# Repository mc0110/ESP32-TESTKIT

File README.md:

# ESP32-TESTKIT

## Motivation
Breadboards are the best or most uncomplicated way to prototype, to test electronic circuit parts quickly and easily or to change them without a soldering iron and without losing the components.

The range of applications for ESP8266 and ESP32 is endless. It is fantastic how quickly and easily practical applications can be realised with this nice devices, which are also super easy to address via WiFi or BLE. They are also very cheap and, like many commercial products (e.g. sonoff, shelly), very reliable. 

The possibilities for using these chips are exorbitantly increased by the great ESPHOME project and also further opened up for prototyping, because it allows the otherwise additionally necessary programming to be reduced to the configuration of a single YAML file. Among other things, it offers the possibility of accessing an elegant web interface, which makes prototypes fantastically easy to implement and test, even if the final programming is to be completely changed afterwards.

** But unfortunately breadboards and ESP-DEVKITS don't really go well together. **

However, if you have ever tried to test your application on a breadboard with a normal TestKIT, the result is somewhat frustrating. I would call it the breadboard paradox. The grid dimension of 2.56mm fits, but all contacts are covered and therefore unusable. There is no chance to contact the individual pins of the board. The required pins must be connected to the board as cables. So you will quickly be faced with a multitude of cable connections that bring with them a high potential for errors during testing. In addition, during my experiments with the ESP32, I found that longer cables in particular can lead to problems with the voltage-supplying lines when the chip wants to establish the WiFi connection, for example, as higher current peaks can obviously occur here.

## Problem definition

This project was therefore about keeping the advantages of ESP-DEVKITS, but resolving the paradox described above and making the CPU pins on the breadboard all available. This makes it extremely convenient to supply power directly to the breadboard. Most DEVKITS have a USB micro-connector and supply the board with 5V as well as 3V3. This would be a requirement that should not be waived. The board should also ensure stable operation of the ESP32 chip, ensuring WiFi setup, etc. without brownout detection or crashes. In addition to the supply via a USB adapter, it could also be helpful to be able to use a 3V3 voltage source (Li-Ion, alkaline batteries) directly.

It has also been shown that there is a need for digital inputs and outputs in almost all circuits. For testing circuits, these should be equipped with signal LEDs to make debugging possible without additional measuring devices, auxiliary circuits, test LEDs. But the ESP32 also offers the possibility to use ADCs and DAC. In order to be able to measure voltages above 3.3V, a suitable voltage divider is needed. Here it would be good to have measurable voltages of up to 15V to cover most applications. Achieving an accuracy of 0.01V is no problem with the ESP32. The ADC functions are masterfully supported by [ESPHOME ADC](https://esphome.io/components/sensor/adc.html?highlight=adc) including the AutoRange function. 

## Provided solution

My ESP32-DEVKIT, which I would like to present here, therefore has the following features:

- USB B micro PowerInput or alternatively
- 12V PlugIn PowerInput
- Input power available as own connector for tests
- DC-DC converter to 3V3
- PGM-socket (shelly-compatible)
- RESET button and GPIO00 button
- 4x 15V ADC-ports (with voltage dividers)
  (V1:GPIO39, V2:GPIO36, V3: GPIO35, V4: GPIO34)
- 4x digital output (LED-controlled) vs. GND-level
  (O1:GPIO21, O2: GPIO22, O3: GPIO23, O4: GPIO25)
- 4x digital input (LED-controlled) vs. GND-level
  (I1:GPIO12, I2: GPIO13, I3: GPIO14, I4: GPIO15)

- all ESP-PINs available on the breadboard

Circuit diagram and board are realised in KICAD V6. The board is 2-layered.

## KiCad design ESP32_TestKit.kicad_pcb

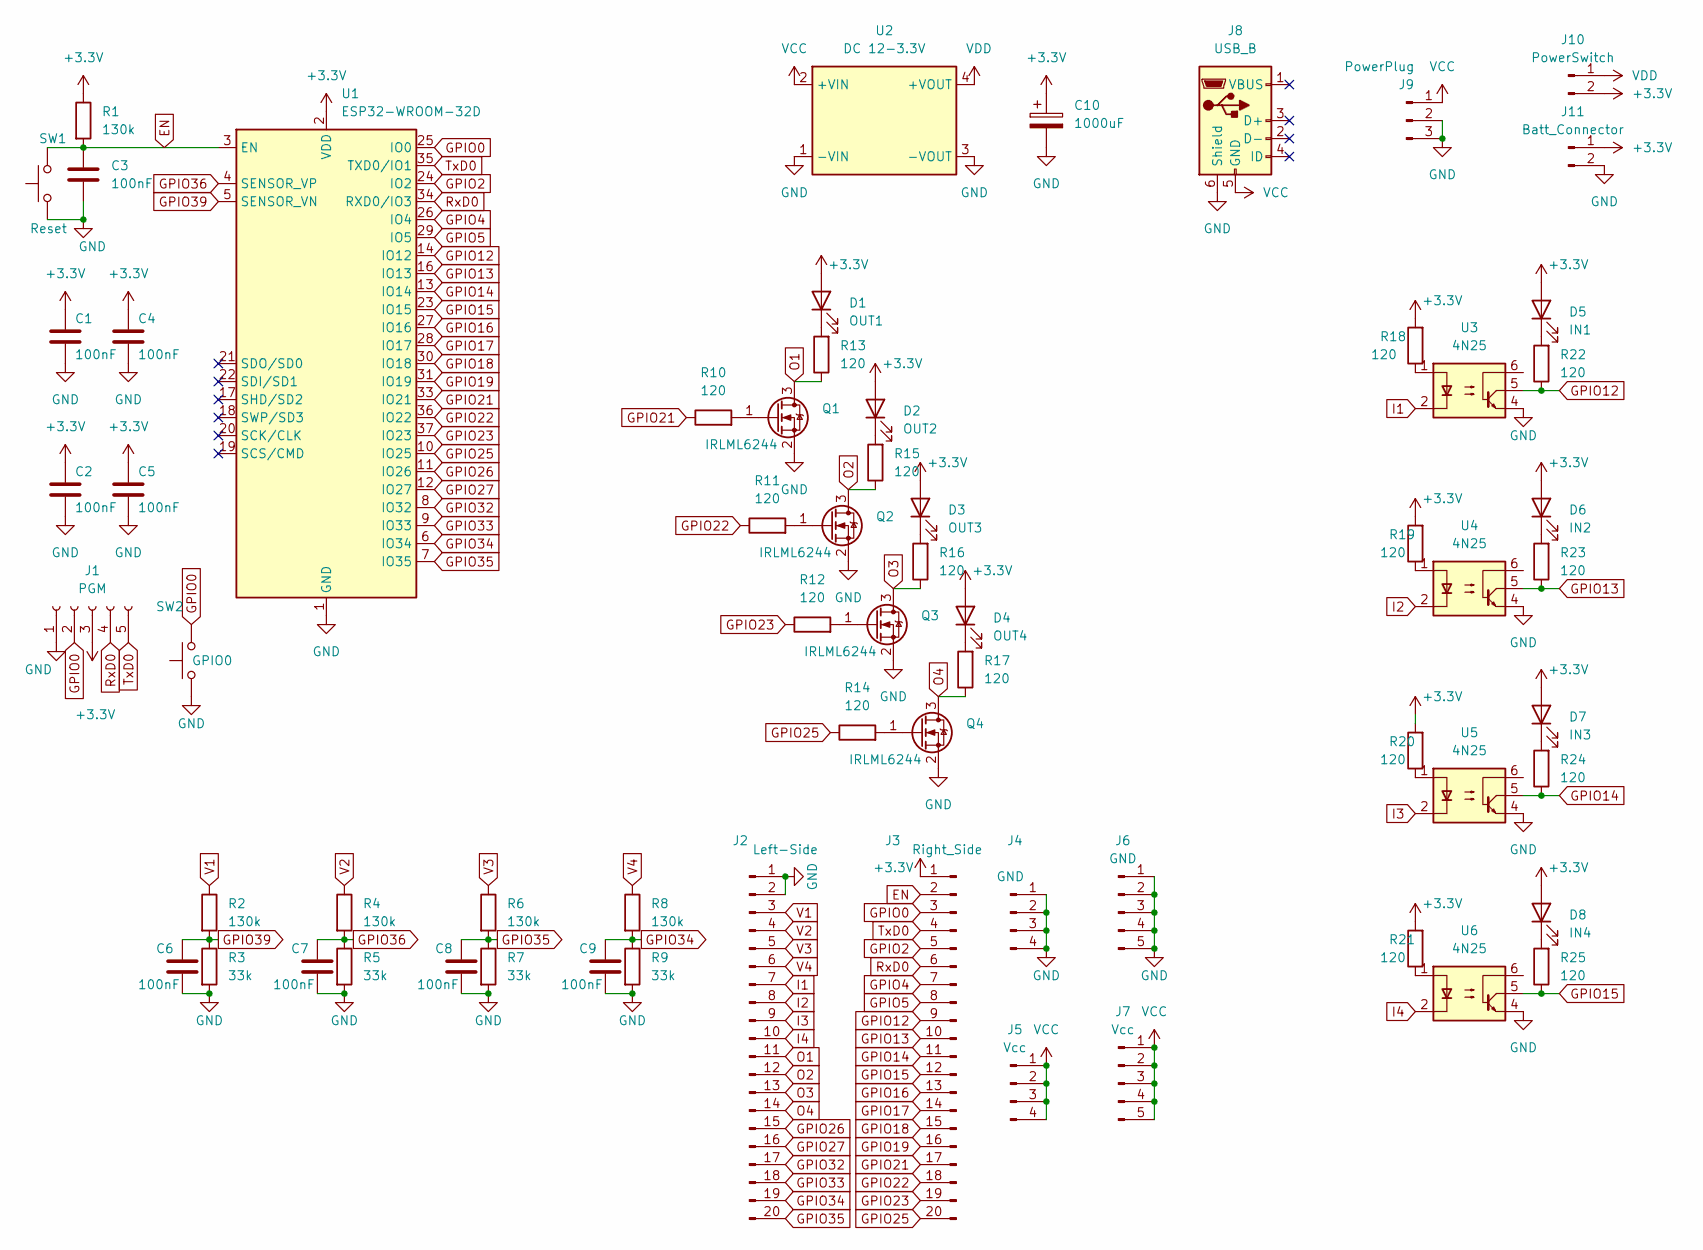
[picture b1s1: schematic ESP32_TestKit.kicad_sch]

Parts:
C1, C2, C3, C4, C5, C6, C7, C8, C9: 100nF; C_Axial_L5.1mm_D3.1mm_P7.50mm_Horizontal
C10: 1000uF; CP_Radial_D10.0mm_P5.00mm
D1: OUT1; LED_D3.0mm
D2: OUT2; LED_D3.0mm
D3: OUT3; LED_D3.0mm
D4: OUT4; LED_D3.0mm
D5: IN1; LED_D3.0mm
D6: IN2; LED_D3.0mm
D7: IN3; LED_D3.0mm
D8: IN4; LED_D3.0mm
J1: PGM; PinSocket_1x05_P2.54mm_Vertical
J2: Left-Side; PinHeader_1x20_P2.54mm_Vertical
J3: Right_Side; PinHeader_1x20_P2.54mm_Vertical
J4: GND; PinHeader_1x04_P2.54mm_Vertical
J5: Vcc; PinHeader_1x04_P2.54mm_Vertical
J6: GND; PinHeader_1x05_P2.54mm_Vertical
J7: Vcc; PinHeader_1x05_P2.54mm_Vertical
J8: USB_B; USB_Micro-AB_Molex_47590-0001
J9: PowerPlug; BarrelJack_GCT_DCJ200-10-A_Horizontal
J10: PowerSwitch; PinHeader_1x02_P2.54mm_Vertical
J11: Batt_Connector; PinHeader_1x02_P2.54mm_Vertical
Q1, Q2, Q3, Q4: IRLML6244; SOT-23
R1, R2, R4, R6, R8: 130k; R_0603_1608Metric
R3, R5, R7, R9: 33k; R_0603_1608Metric
R10, R11, R12, R13, R14, R15, R16, R17, R18, R19, R20, R21, R22, R23, R24, R25: 120; R_0603_1608Metric
SW1: Reset; SW_SPST_PTS645
SW2: GPIO0; SW_SPST_PTS645
U1: ESP32-WROOM-32D; ESP32-WROOM-32
U2: DC 12-3.3V; Converter_DCDC_China3A_THT
U3, U4, U5, U6: 4N25; DIP-6_W7.62mm

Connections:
+3V3: C1.1, C2.1, C4.1, C5.1, C10.1, D1.2 (A), D2.2 (A), D3.2 (A), D4.2 (A), D5.2 (A), D6.2 (A), D7.2 (A), D8.2 (A), J1.3, J3.1, J10.2, J11.1, R1.1, R18.2, R19.2, R20.2, R21.2, U1.2 (VDD)
EN: C3.1, J3.2, R1.2, SW1.2, U1.3 (EN)
GND: C1.2, C2.2, C3.2, C4.2, C5.2, C6.2, C7.2, C8.2, C9.2, C10.2, J1.1, J2.1, J2.2, J4.1, J4.2, J4.3, J4.4, J6.1, J6.2, J6.3, J6.4, J6.5, J8.6 (Shield), J9.2, J9.3, J11.2, Q1.2 (S), Q2.2 (S), Q3.2 (S), Q4.2 (S), R3.2, R5.2, R7.2, R9.2, SW1.1, SW2.1, U1.1 (GND), U1.15 (GND), U1.38 (GND), U1.39 (GND), U2.1 (-VIN), U2.3 (-VOUT), U3.4, U4.4, U5.4, U6.4
GPIO0: J1.2, J3.3, SW2.2, U1.25 (IO0)
GPIO2: J3.5, U1.24 (IO2)
GPIO4: J3.7, U1.26 (IO4)
GPIO5: J3.8, U1.29 (IO5)
GPIO12: J3.9, R22.1, U1.14 (IO12), U3.5
GPIO13: J3.10, R23.1, U1.16 (IO13), U4.5
GPIO14: J3.11, R24.1, U1.13 (IO14), U5.5
GPIO15: J3.12, R25.1, U1.23 (IO15), U6.5
GPIO16: J3.13, U1.27 (IO16)
GPIO17: J3.14, U1.28 (IO17)
GPIO18: J3.15, U1.30 (IO18)
GPIO19: J3.16, U1.31 (IO19)
GPIO21: J3.17, R10.1, U1.33 (IO21)
GPIO22: J3.18, R11.1, U1.36 (IO22)
GPIO23: J3.19, R12.1, U1.37 (IO23)
GPIO25: J3.20, R14.1, U1.10 (IO25)
GPIO26: J2.15, U1.11 (IO26)
GPIO27: J2.16, U1.12 (IO27)
GPIO32: J2.17, U1.8 (IO32)
GPIO33: J2.18, U1.9 (IO33)
GPIO34: C9.1, J2.19, R8.2, R9.1, U1.6 (IO34)
GPIO35: C8.1, J2.20, R6.2, R7.1, U1.7 (IO35)
GPIO36: C7.1, R4.2, R5.1, U1.4 (SENSOR_VP)
GPIO39: C6.1, R2.2, R3.1, U1.5 (SENSOR_VN)
I1: J2.7, U3.2
I2: J2.8, U4.2
I3: J2.9, U5.2
I4: J2.10, U6.2
unnamed: D1.1 (K), R13.2
unnamed: D2.1 (K), R15.2
unnamed: D3.1 (K), R16.2
unnamed: D4.1 (K), R17.2
unnamed: D5.1 (K), R22.2
unnamed: D6.1 (K), R23.2
unnamed: D7.1 (K), R24.2
unnamed: D8.1 (K), R25.2
unnamed: Q1.1 (G), R10.2
unnamed: Q2.1 (G), R11.2
unnamed: Q3.1 (G), R12.2
unnamed: Q4.1 (G), R14.2
unnamed: R18.1, U3.1
unnamed: R19.1, U4.1
unnamed: R20.1, U5.1
unnamed: R21.1, U6.1
O1: J2.11, Q1.3 (D), R13.1
O2: J2.12, Q2.3 (D), R15.1
O3: J2.13, Q3.3 (D), R16.1
O4: J2.14, Q4.3 (D), R17.1
RxD0: J1.4, J3.6, U1.34 (RXD0/IO3)
TxD0: J1.5, J3.4, U1.35 (TXD0/IO1)
V1: J2.3, R2.1
V2: J2.4, R4.1
V3: J2.5, R6.1
V4: J2.6, R8.1
VCC: J5.1, J5.2, J5.3, J5.4, J7.1, J7.2, J7.3, J7.4, J7.5, J8.5 (GND), J9.1, U2.2 (+VIN)
VDD: J10.1, U2.4 (+VOUT)

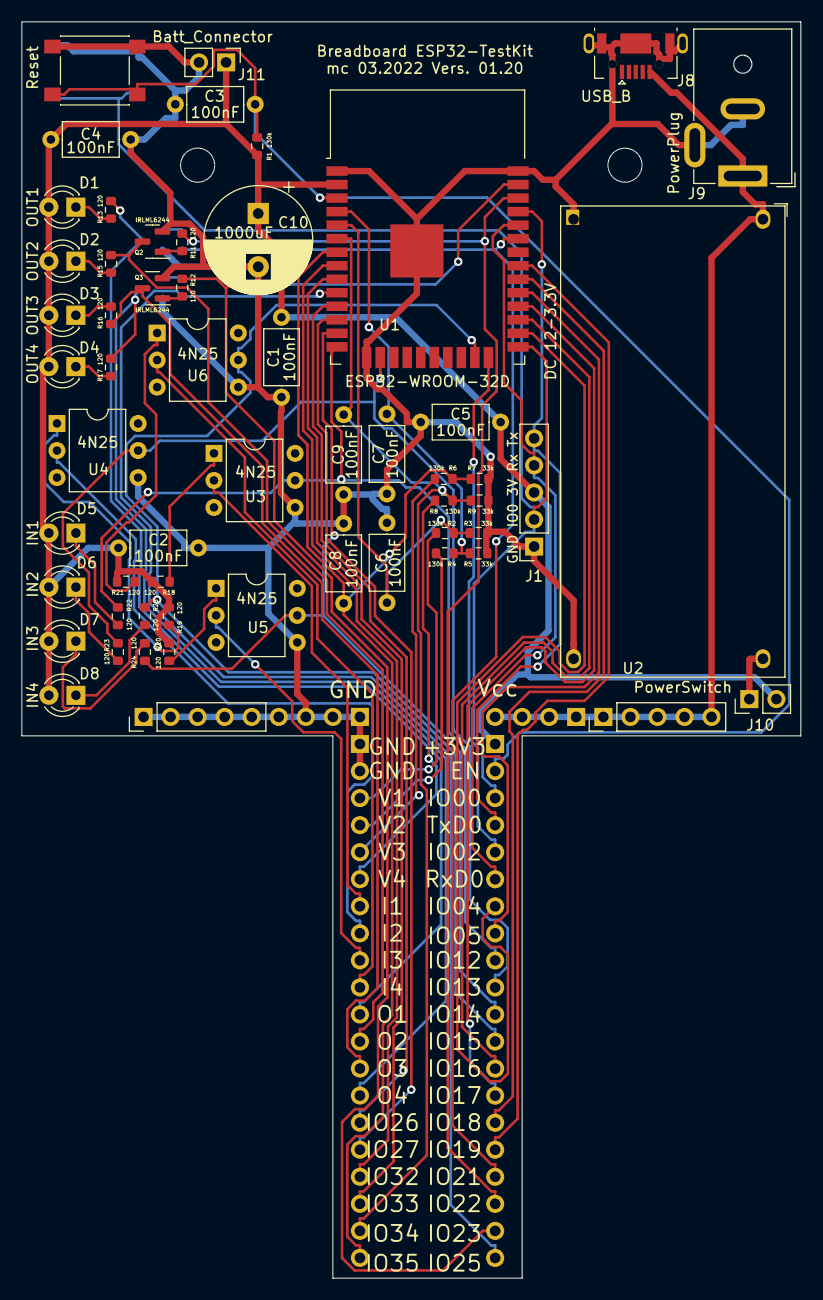
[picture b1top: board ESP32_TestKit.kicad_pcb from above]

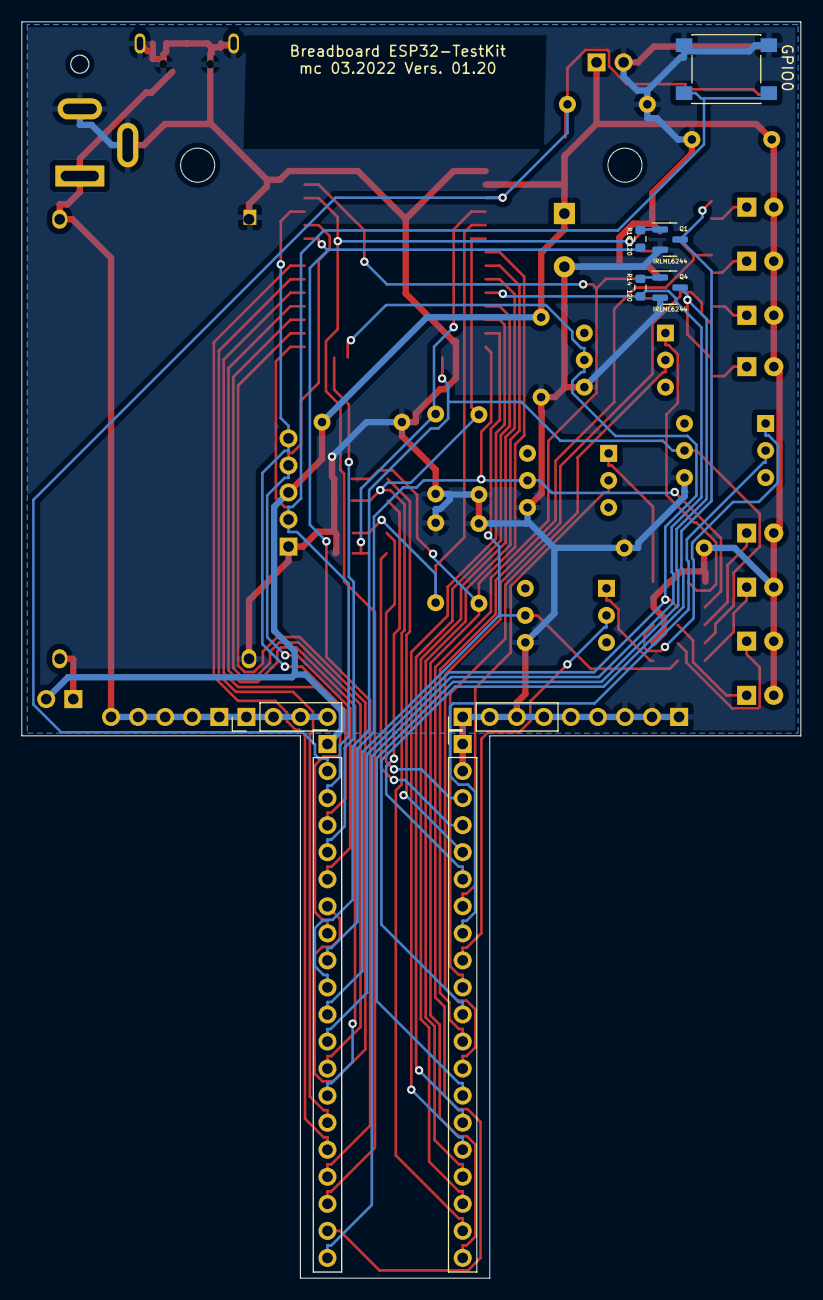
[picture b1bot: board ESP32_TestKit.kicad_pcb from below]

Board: 2 copper layers, 73.1 x 118.0 mm, 68 parts (9 on the bottom side), 59 nets.

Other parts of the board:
REF1, REF2: MountingHole_3.2mm_M3

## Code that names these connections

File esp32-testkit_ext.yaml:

# configuration for ESP32 Testkit
# 
substitutions:
  device_name: esp32-testkit
  ui: 100ms # Update Intervall for Window-Size
  ws: '10' # Window Size -> 1s 
  se: '5' # send every -> send every 500ms
  ui1: 1s  # Update Intervall for Template-Sensors

esphome:
  name: ${device_name}
  platform: ESP32
  board: lolin32
  on_boot:
    then:
      - switch.turn_on: o1

wifi:
  ssid: "xxxxxx"
  password: "xxxxxx"

  ap:
    ssid: ${device_name}_hotspot
    password: "12345678"

captive_portal:

# Enable logging
logger:

# Enable OTA updates
ota:
  safe_mode: true
 
# Enable Web server (optional).
web_server:
  port: 80

text_sensor:
  # Expose ESPHome version as sensor.
  - platform: version
    name: ${device_name}_ESPHome_version
  # Expose WiFi information as sensors.
  - platform: wifi_info
    ip_address:
      name: ${device_name}_IP
    ssid:
      name: ${device_name}_SSID
    bssid:
      name: ${device_name}_BSSID
  - platform: template
    name: ${device_name}_up_hr
    id: uptime_human
    icon: mdi:clock-start

# Sensors with general information.
sensor:
  # Uptime sensor
  - platform: uptime
    name: ${device_name}_uptime
    id: uptime_sensor
    update_interval: 60s
    on_raw_value:
      then:
        - text_sensor.template.publish:
            id: uptime_human
            state: !lambda |-
              int seconds = round(id(uptime_sensor).raw_state);
              int days = seconds / (24 * 3600);
              seconds = seconds % (24 * 3600);
              int hours = seconds / 3600;
              seconds = seconds % 3600;
              int minutes = seconds /  60;
              seconds = seconds % 60;
              return (
                (days ? String(days) + "d " : "") +
                (hours ? String(hours) + "h " : "") +
                (minutes ? String(minutes) + "m " : "") +
                (String(seconds) + "s")
              ).c_str();
  # WiFi Signal sensor.
  - platform: wifi_signal
    name: ${device_name}_wifi_signal
    update_interval: 60s

  - platform: adc
    pin: GPIO39
    id: v39
    name: "V1 bis 12V"
    unit_of_measurement: "V"    
    accuracy_decimals: 3
    attenuation: auto
    update_interval: ${ui}
    filters:
      - sliding_window_moving_average:
          window_size: ${ws}
          send_every: ${se}
      - offset: 0
      - multiply: 4.9393939  # 1/ 33/153

  - platform: adc
    pin: GPIO36
    id: v36
    name: "V2 bis 12V"
    unit_of_measurement: "V"    
    accuracy_decimals: 3
    attenuation: auto
    update_interval: ${ui}
    filters:
      - sliding_window_moving_average:
          window_size: ${ws}
          send_every: ${se}
      - offset: 0
      - multiply: 4.9393939  # 1/ 33/153

  - platform: adc
    pin: GPIO35
    id: v35
    name: "V3 bis 12V"
    unit_of_measurement: "V"    
    accuracy_decimals: 3
    attenuation: auto
    update_interval: ${ui}
    filters:
      - sliding_window_moving_average:
          window_size: ${ws}
          send_every: ${se}
      - offset: 0
      - multiply: 4.9393939  # 1/ 33/153

  - platform: adc
    pin: GPIO34
    id: v34
    name: "V4 bis 12V"
    unit_of_measurement: "V"    
    accuracy_decimals: 3
    attenuation: auto
    update_interval: ${ui}
    filters:
      - sliding_window_moving_average:
          window_size: ${ws}
          send_every: ${se}
      - offset: 0
      - multiply: 4.9393939  # 1/ 33/153

binary_sensor:
  - platform: gpio
    pin:
      number: GPIO12
      mode:
        input: true
        pullup: true
      inverted: true
    name: "I1"
    id: i1

  - platform: gpio
    pin:
      number: GPIO13
      mode:
        input: true
        pullup: true
      inverted: true
    name: "I2"
    id: i2

  - platform: gpio
    pin:
      number: GPIO14
      mode:
        input: true
        pullup: true
      inverted: true
    name: "I3"
    id: i3

  - platform: gpio
    pin:
      number: GPIO15
      mode:
        input: true
        pullup: true
      inverted: true
    name: "I4"
    id: i4

switch:
  - platform: gpio
    id: o1
    name: "O1"
    restore_mode: ALWAYS_OFF 
    pin:
      number: GPIO21
      inverted: false
    on_turn_on:
      - delay: 2s
      - switch.turn_off: o1
    on_turn_off:
      - delay: 2s
      - switch.turn_on: o1
    
  - platform: gpio
    id: o2
    name: "O2"
    restore_mode: ALWAYS_OFF 
    pin:
      number: GPIO22
      inverted: false

  - platform: gpio
    id: o3
    name: "O3"
    restore_mode: ALWAYS_OFF 
    pin:
      number: GPIO23
      inverted: false

  - platform: gpio
    id: o4
    name: "O4"
    restore_mode: ALWAYS_OFF 
    pin:
      number: GPIO25
      inverted: false

output:
  - platform: esp32_dac
    pin: GPIO26
    id: dac_output

fan:
  - platform: speed
    output: dac_output
    name: "DAC"

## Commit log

2022-04-02 Add files via upload
    C1
2022-10-06 Create Example.yaml
    YAML-File added
2023-10-04 modified: KIT_Bottomside.jpg modified: KIT_UpperSide.jpg
